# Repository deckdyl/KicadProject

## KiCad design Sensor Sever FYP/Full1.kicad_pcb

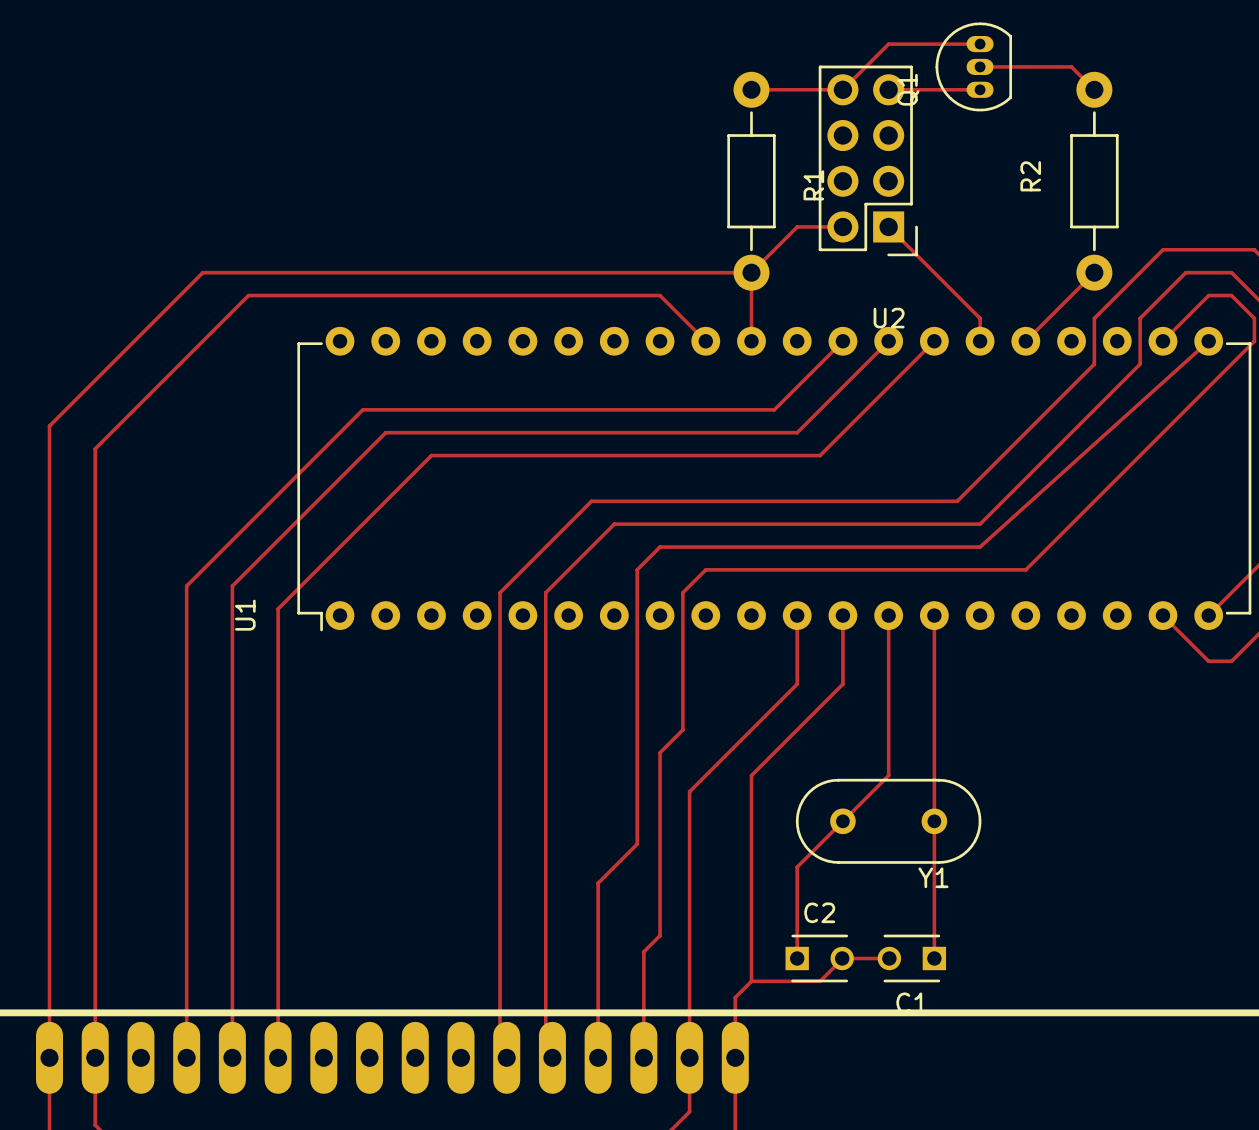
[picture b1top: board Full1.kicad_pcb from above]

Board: 2 copper layers, 9 parts (0 on the bottom side), 16 nets.

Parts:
C1, C2: 22pF; C_Disc_D3_P2.5
DP1: LCD-20X4; LCD-20x4
Q1: 2N3904; TO-92_Inline_Narrow_Oval
R1: 10kΩ; Resistor_Horizontal_RM10mm
R2: 1.2kΩ; Resistor_Horizontal_RM10mm
U1: PIC18F4550; DIP-40_W15.24mm
U2: ESP-8266; Pin_Header_Straight_2x04
Y1: 20Mhz; HC-49V

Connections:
3V3: Q1.1, U2.7
+5V: DP1.2, DP1.15, U1.11, U1.32
GND: C1.2, C2.2, DP1.1, DP1.16, R1.2, U1.12, U1.31, U2.2
LCD_EN: DP1.6, U1.27
LCD_RS: DP1.4, U1.29
LCD_RW: DP1.5, U1.28
unnamed: C2.1, U1.13, Y1.2
unnamed: DP1.11, U1.19
unnamed: DP1.12, U1.20
unnamed: DP1.13, U1.21
unnamed: DP1.14, U1.22
unnamed: Q1.2, R2.2
unnamed: Q1.3, R1.1, U2.8
unnamed: R2.1, U1.25
OSC2: C1.1, U1.14, Y1.1
PIC_RX: U1.26, U2.1

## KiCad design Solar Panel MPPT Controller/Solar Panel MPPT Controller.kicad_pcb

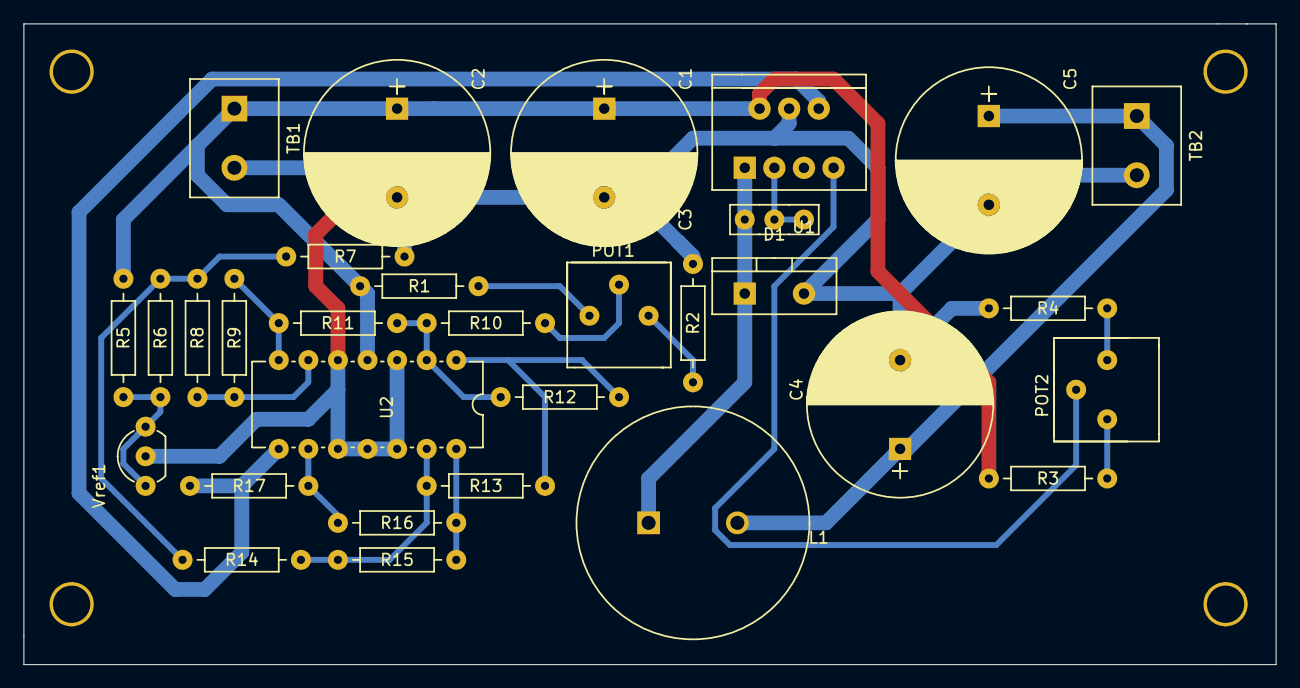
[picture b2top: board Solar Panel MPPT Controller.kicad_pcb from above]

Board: 2 copper layers, 107.5 x 55.0 mm, 31 parts (0 on the bottom side), 21 nets.

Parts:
C1, C2, C4, C5: 2.2mF; Cap_Pol_Radial_D16_P4
C3: 10nF; Cap_UnPol_P3
D1: STPS10L25D; TO-220_Neutral12_Vertical
L1: 22uH; Inductor-22uH-5.4A
POT1, POT2: 2kΩ; Potentiometer_Bourns_3386
R1, R3: 82kΩ; Resistor-0.25W
R2: 5.6kΩ; Resistor-0.25W
R4, R7: 9.1kΩ; Resistor-0.25W
R5: 3.3kΩ; Resistor-0.25W
R6, R8, R9: 10kΩ; Resistor-0.25W
R10, R11, R12, R13, R14, R15, R16, R17: 100kΩ; Resistor-0.25W
TB1: Panel In; Terminal_Block-5mm
TB2: Output; Terminal_Block-5mm
U1: LM2678T-ADJ; TO-220_Neutral1234567_Vertical
U2: TL084; IC_PDIP_14pin
Vref1: TL431; TO-92_Inline_Wide

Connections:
1.19V: R6.1, R7.2, R8.1, R14.1
GND: C1.2, C2.2, C4.2, C5.2, D1.2, R2.1, R4.2, R7.1, TB1.2, TB2.2, U1.4, U2.3, U2.5, U2.10, U2.11, U2.12, Vref1.2
unnamed: C3.1, D1.1, L1.1, U1.1
unnamed: C3.2, U1.3
unnamed: C4.1, C5.1, L1.2, TB2.1
unnamed: POT1.1, R1.2
unnamed: POT1.2, R10.1
unnamed: POT1.3, R2.2
unnamed: POT2.1, R3.2
unnamed: POT2.2, U1.7
unnamed: POT2.3, R4.1
unnamed: R5.1, R6.2, Vref1.1, Vref1.3
unnamed: R8.2, R9.1, U2.6
unnamed: R10.2, R11.2, R12.1, U2.2
unnamed: R9.2, R11.1, U2.7
unnamed: R12.2, R13.1, U2.1
unnamed: R13.2, R14.2, R15.1, U2.13
unnamed: R15.2, R16.1, U2.14
unnamed: R16.2, R17.1, U2.9
unnamed: R17.2, U1.6, U2.8
Vin: C1.1, C2.1, R1.1, R3.1, R5.2, TB1.1, U1.2, U2.4

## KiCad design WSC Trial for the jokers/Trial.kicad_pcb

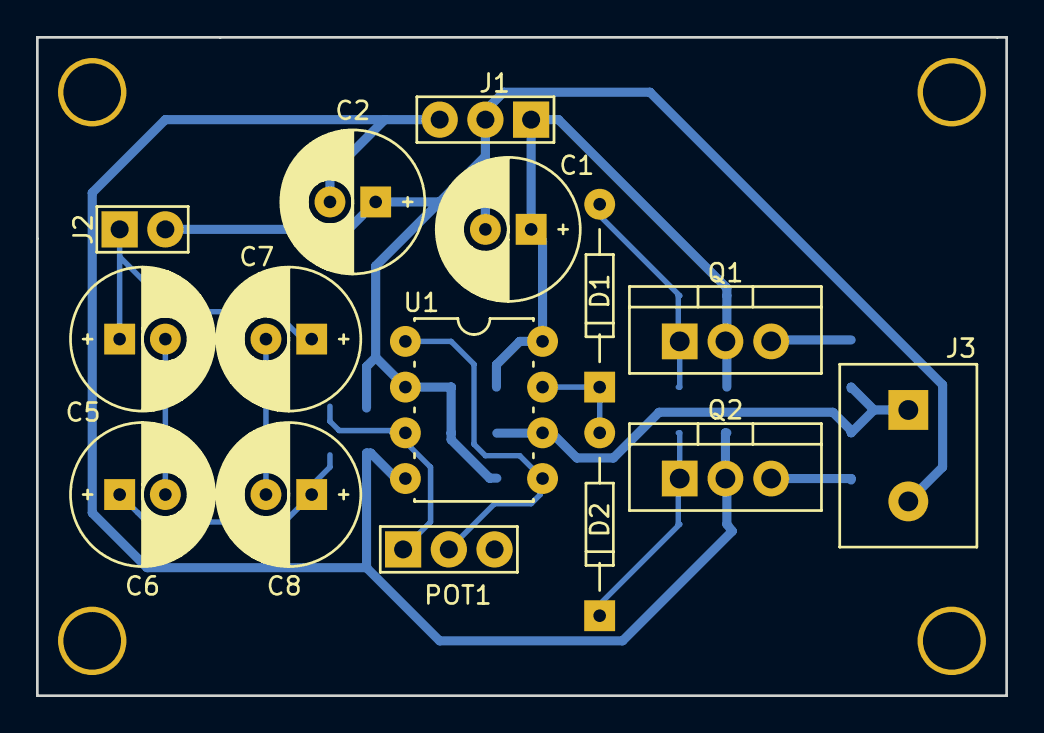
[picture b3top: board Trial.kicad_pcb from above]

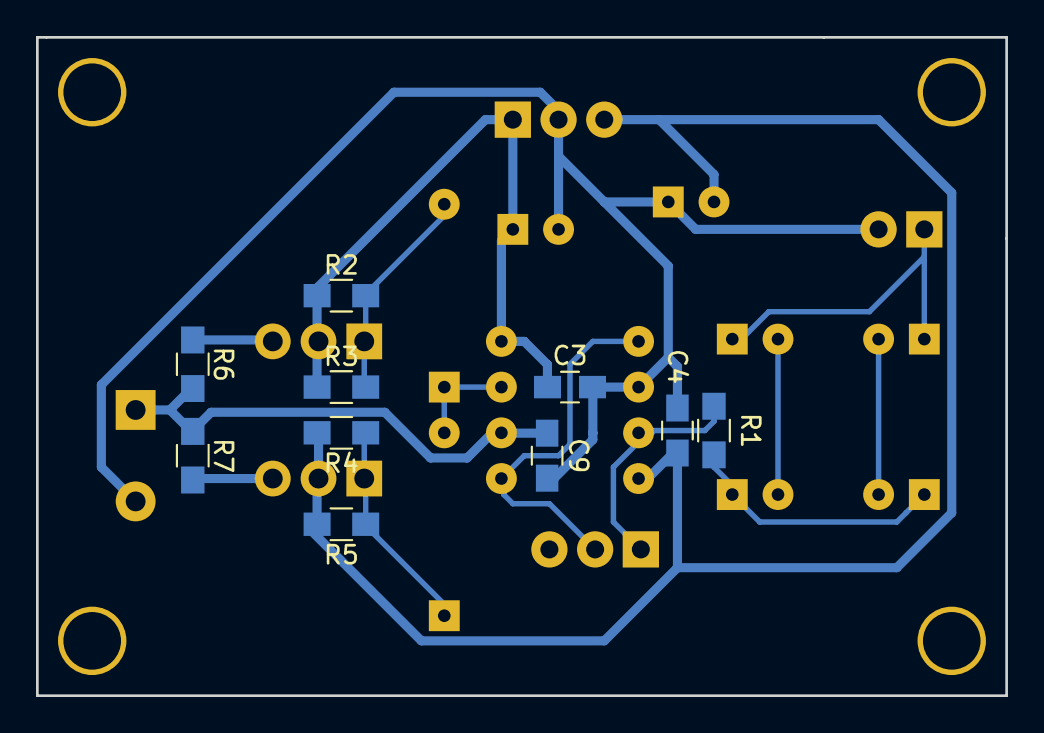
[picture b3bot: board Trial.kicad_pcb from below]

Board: 2 copper layers, 53.8 x 36.6 mm, 25 parts (10 on the bottom side), 15 nets.

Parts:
C1, C2, C5, C6, C7, C8: 22uF; Cap_Pol_Radial_D8_P2
C3, C4: 100nF; C_0805_HandSoldering
C9: 10nF; C_0805_HandSoldering
D1, D2: 1N4148
J1: Power In; Pin_Header_Straight_1x03
J2: Signal In; Pin_Header_Straight_1x02
J3: Signal Out; Terminal_Block-5mm
POT1: 10kΩ; Pin_Header_Straight_1x03
Q1: TIP31; TO-220_Neutral123_Vertical
Q2: TIP32; TO-220_Neutral123_Vertical
R1: 100Ω; R_0805_HandSoldering
R2, R3, R4, R5: 10kΩ; R_0805_HandSoldering
R6, R7: 2Ω; R_0805_HandSoldering
U1: LM358; IC_PDIP_8pin

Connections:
+12V: C1.1, C3.1, J1.1, Q1.2, R2.1, R3.1, U1.8
-12V: C2.2, C4.2, J1.3, Q2.2, R4.2, R5.2, U1.4
GND: C1.2, C2.1, C3.2, C4.1, C9.2, J1.2, J2.2, J3.2, U1.2
unnamed: C5.1, C7.1, J2.1
unnamed: C5.2, C6.2
unnamed: C6.1, C8.1, R1.1
unnamed: C7.2, C8.2
unnamed: C9.1, J3.1, R6.2, R7.1, U1.6
unnamed: D1.1, D2.2, U1.7
unnamed: D1.2, Q1.1, R2.2, R3.2
unnamed: D2.1, Q2.1, R4.1, R5.1
unnamed: POT1.1, R1.2, U1.3
unnamed: POT1.2, U1.1, U1.5
unnamed: Q1.3, R6.1
unnamed: Q2.3, R7.2
